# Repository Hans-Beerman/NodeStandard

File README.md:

**NodeStandard**

NodeStandard is the base for different nodes, used at the MakerSpace Leiden, to control different pieces of equipment. This repository has the following subdirs:

- **Drawings:**

- **Gerber_Files:**

This directory contains the Gerber files for production of the print. In this directory are the separate files and a *.ZIP file containing all these files. For ordering the printed circuit board, for example from JLCPCB, you only need to upload the ZIP file

Schematic of the wiring between the different modules used

- **KiCad\_files:**

The design of the PCB for the Node/Controller. De PCB in this design is not meant to be used for a real PCB. It is used as guideline for a handmade PCB

- **Photos:**

Some photos of the Node made.

- **PlatformIO\_Files:**

The source code for the Node and the display used. For the development of this software PlatformIO is used. PlatformIO is an Extension on Visual Studio Code.

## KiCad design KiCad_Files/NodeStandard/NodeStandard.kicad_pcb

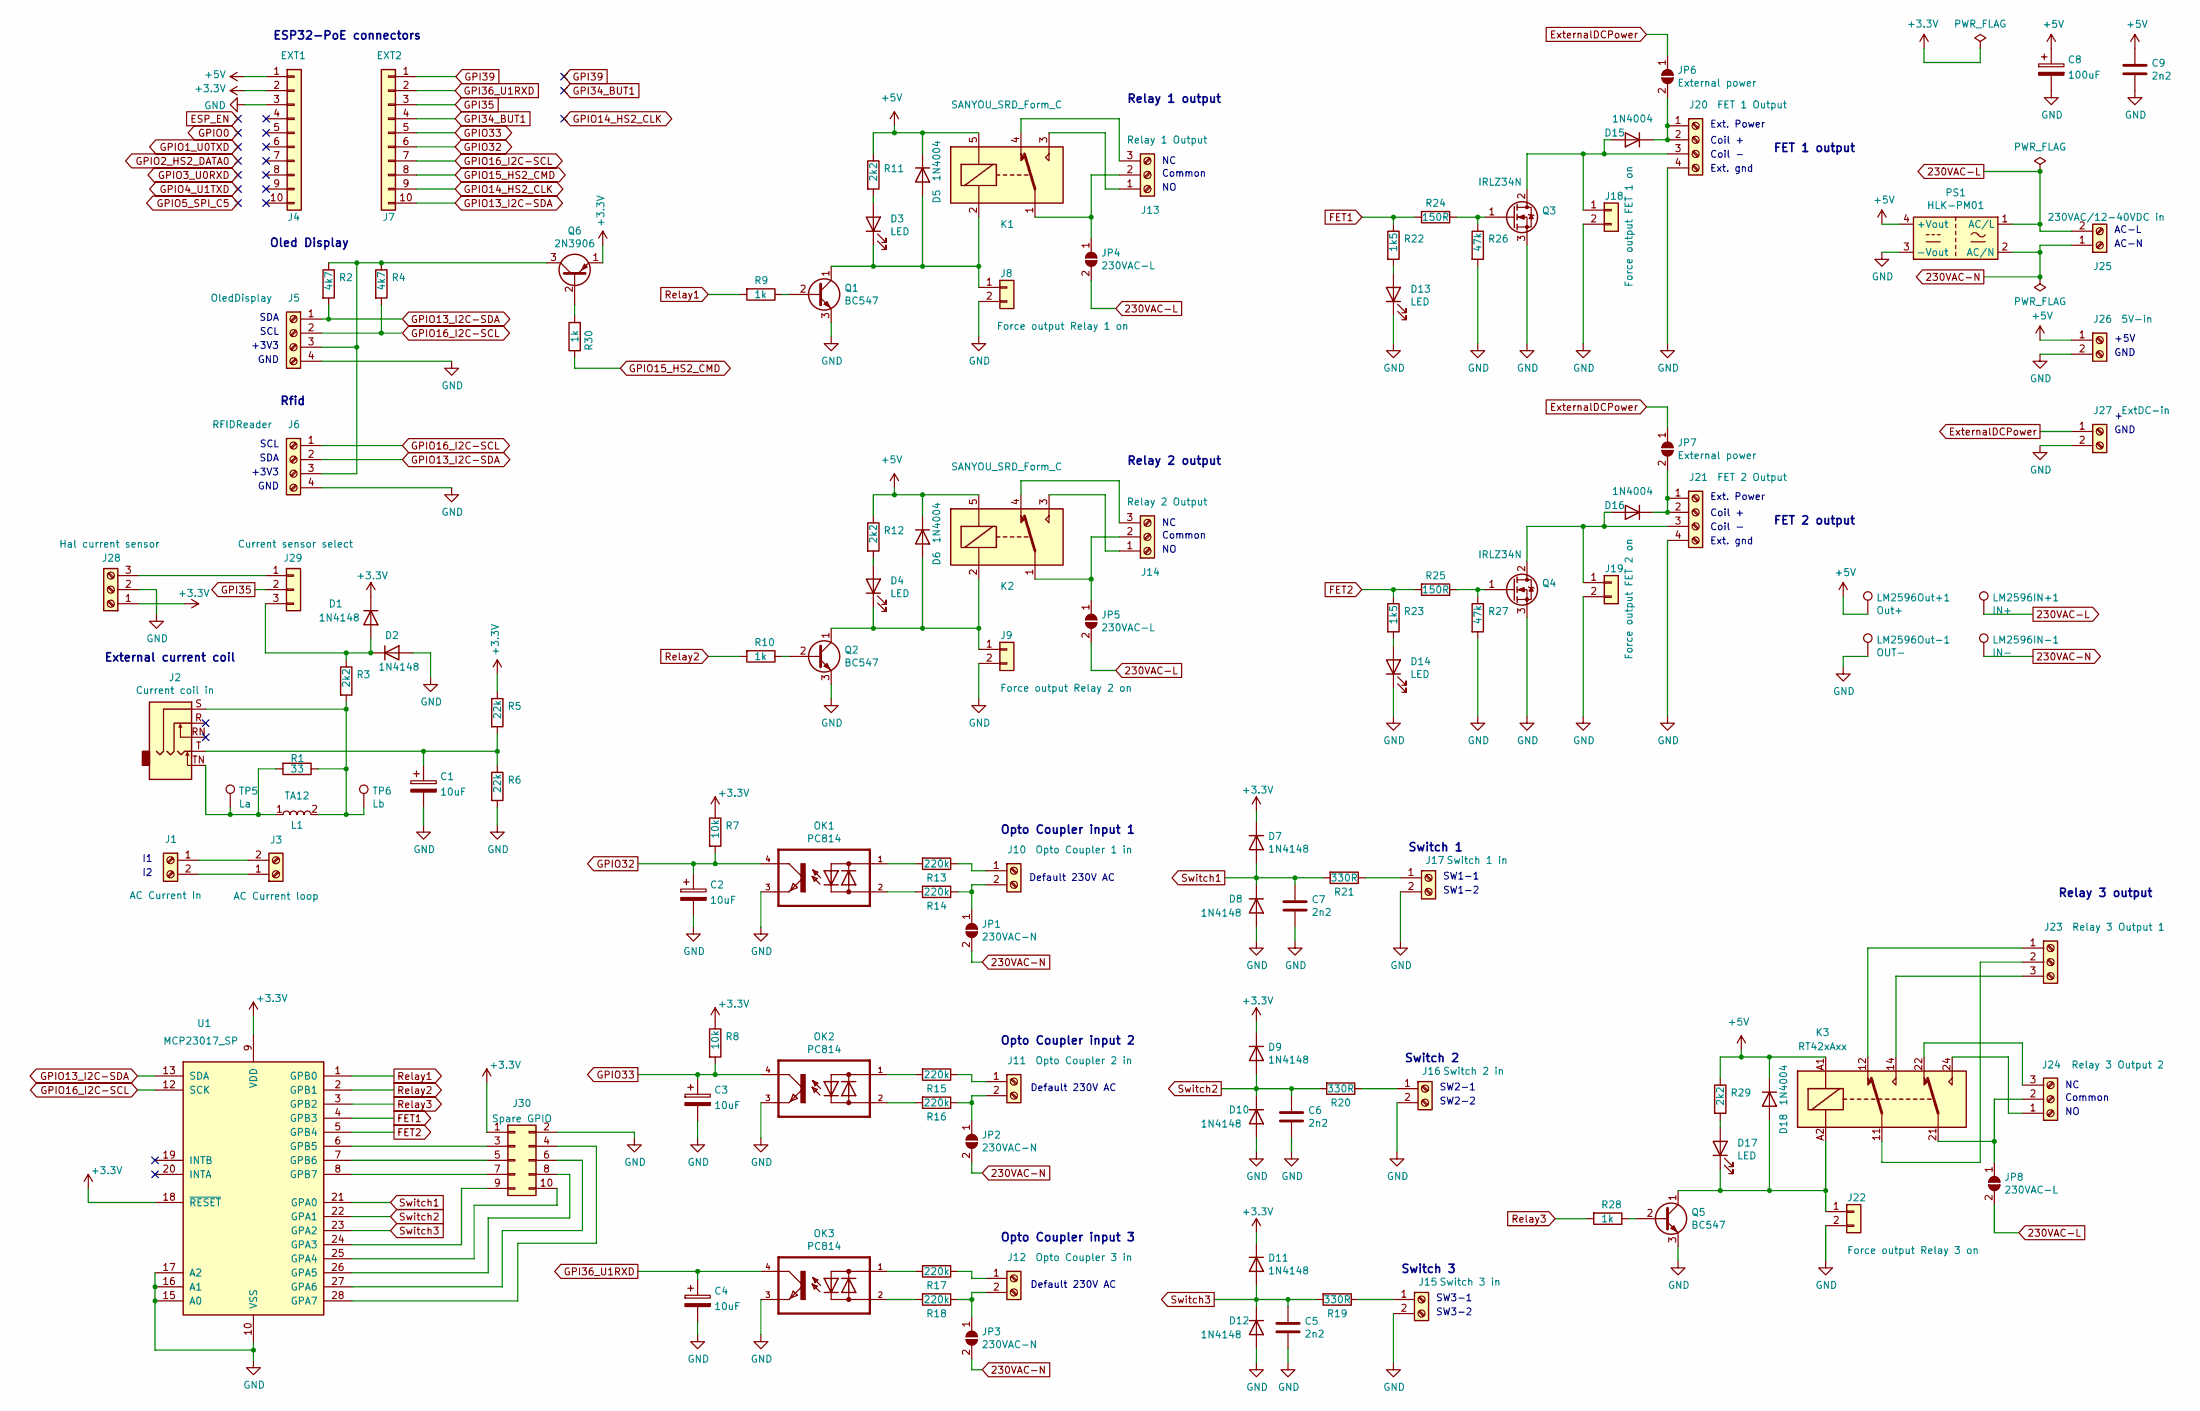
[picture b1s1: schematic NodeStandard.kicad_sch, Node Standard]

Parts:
C1, C2, C3, C4: 10uF; CP_Radial_D6.3mm_P2.50mm
C5, C6, C7, C9: 2n2; C_Disc_D5.1mm_W3.2mm_P5.00mm
C8: 100uF; CP_Radial_D6.3mm_P2.50mm
D1, D2, D7, D8, D9, D10, D11, D12: 1N4148; D_DO-35_SOD27_P7.62mm_Horizontal
D3, D4, D13, D14, D17: LED; LED_D3.0mm
D5, D6, D15, D16, D18: 1N4004; D_DO-41_SOD81_P10.16mm_Horizontal
J1: AC Current In; PhoenixContact_MSTB_2,5_2-GF-5,08_1x02_P5.08mm_Horizontal_T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
J2: Current coil in; Jack_3.5mm_CUI_FEMPM_Horizontal
J3: AC Current loop; TerminalBlock_Phoenix_MKDS-1,5-2-5.08_1x02_P5.08mm_Horizont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
J4: EXT1; PinSocket_1x10_P2.54mm_Vertical
J5: OledDisplay; TerminalBlock_Phoenix_MPT-0,5-4-2.54_1x04_P2.54mm_Horizontal
J6: RFIDReader; TerminalBlock_Phoenix_MPT-0,5-4-2.54_1x04_P2.54mm_Horizontal
J7: EXT2; PinSocket_1x10_P2.54mm_Vertical
J8: Force output Relay 1 on; PinHeader_1x02_P2.54mm_Vertical
J9: Force output Relay 2 on; PinHeader_1x02_P2.54mm_Vertical
J10: Opto Coupler 1 in; PhoenixContact_MSTB_2,5_2-GF-5,08_1x02_P5.08mm_Horizontal_T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
J11: Opto Coupler 2 in; PhoenixContact_MSTB_2,5_2-GF-5,08_1x02_P5.08mm_Horizontal_T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
J12: Opto Coupler 3 in; PhoenixContact_MSTB_2,5_2-GF-5,08_1x02_P5.08mm_Horizontal_T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
J13: Relay 1 Output; PhoenixContact_MSTB_2,5_3-GF-5,08_1x03_P5.08mm_Horizontal_T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
J14: Relay 2 Output; PhoenixContact_MSTB_2,5_3-GF-5,08_1x03_P5.08mm_Horizontal_T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
J15: Switch 3 in; TerminalBlock_Phoenix_MPT-0,5-2-2.54_1x02_P2.54mm_Horizontal
J16: Switch 2 in; TerminalBlock_Phoenix_MPT-0,5-2-2.54_1x02_P2.54mm_Horizontal
J17: Switch 1 in; TerminalBlock_Phoenix_MPT-0,5-2-2.54_1x02_P2.54mm_Horizontal
J18: Force output FET 1 on; PinHeader_1x02_P2.54mm_Vertical
J19: Force output FET 2 on; PinHeader_1x02_P2.54mm_Vertical
J20: FET 1 Output; PhoenixContact_MSTB_2,5_4-GF-5,08_1x04_P5.08mm_Horizontal_T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
J21: FET 2 Output; PhoenixContact_MSTB_2,5_4-GF-5,08_1x04_P5.08mm_Horizontal_T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
J22: Force output Relay 3 on; PinHeader_1x02_P2.54mm_Vertical
J23: Relay 3 Output 1; PhoenixContact_MSTB_2,5_3-GF-5,08_1x03_P5.08mm_Horizontal_T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
J24: Relay 3 Output 2; PhoenixContact_MSTB_2,5_3-GF-5,08_1x03_P5.08mm_Horizontal_T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
J25: 230VAC/12-40VDC in; PhoenixContact_MSTB_2,5_2-GF-5,08_1x02_P5.08mm_Horizontal_T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
J26: 5V-in; PhoenixContact_MSTB_2,5_2-GF-5,08_1x02_P5.08mm_Horizontal_T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
J27: ExtDC-in; PhoenixContact_MSTB_2,5_2-GF-5,08_1x02_P5.08mm_Horizontal_T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
J28: Hal current sensor; TerminalBlock_Phoenix_MPT-0,5-3-2.54_1x03_P2.54mm_Horizontal
J29: Current sensor select; PinHeader_1x03_P2.54mm_Vertical
J30: Spare GPIO; PinHeader_2x05_P2.54mm_Vertical
JP1, JP2, JP3: 230VAC-N; SolderJumper-2_P3mm_Open_RoundedPad
JP4, JP5, JP8: 230VAC-L; SolderJumper-2_P3mm_Open_RoundedPad
JP6, JP7: External power; SolderJumper-2_P1.3mm_Open_RoundedPad1.0x1.5mm
K1, K2: SANYOU_SRD_Form_C; Relay_SPDT_SANYOU_SRD_Series_Form_C
K3: RT42xAxx; Relay_DPDT_Schrack-RT2-FormC_RM5mm
L1: TA12; TA12-100
LM2596IN+1: IN+; TestPoint_THTPad_2.0x2.0mm_Drill1.0mm
LM2596IN-1: IN-; TestPoint_THTPad_2.0x2.0mm_Drill1.0mm
LM2596Out+1: Out+; TestPoint_THTPad_2.0x2.0mm_Drill1.0mm
LM2596Out-1: OUT-; TestPoint_THTPad_2.0x2.0mm_Drill1.0mm
OK1, OK2, OK3: PC814; DIP-4_W7.62mm
PS1: HLK-PM01; Converter_ACDC_HiLink_HLK-PMxx
Q1, Q2, Q5: BC547; TO-92_Inline
Q3, Q4: IRLZ34N; TO-220-3_Vertical
Q6: 2N3906; TO-92_Inline
R1: 33; R_Axial_DIN0207_L6.3mm_D2.5mm_P7.62mm_Horizontal
R2, R4: 4k7; R_Axial_DIN0207_L6.3mm_D2.5mm_P7.62mm_Horizontal
R3, R11, R12, R29: 2k2; R_Axial_DIN0207_L6.3mm_D2.5mm_P7.62mm_Horizontal
R5, R6: 22k; R_Axial_DIN0207_L6.3mm_D2.5mm_P7.62mm_Horizontal
R7, R8: 10k; R_Axial_DIN0207_L6.3mm_D2.5mm_P7.62mm_Horizontal
R9, R10, R28, R30: 1k; R_Axial_DIN0207_L6.3mm_D2.5mm_P7.62mm_Horizontal
R13, R14, R15, R16, R17, R18: 220k; R_Axial_DIN0516_L15.5mm_D5.0mm_P20.32mm_Horizontal
R19, R20, R21: 330R; R_Axial_DIN0207_L6.3mm_D2.5mm_P7.62mm_Horizontal
R22, R23: 1k5; R_Axial_DIN0207_L6.3mm_D2.5mm_P7.62mm_Horizontal
R24, R25: 150R; R_Axial_DIN0207_L6.3mm_D2.5mm_P7.62mm_Horizontal
R26, R27: 47k; R_Axial_DIN0207_L6.3mm_D2.5mm_P7.62mm_Horizontal
TP5: La; TestPoint_THTPad_2.5x2.5mm_Drill1.2mm
TP6: Lb; TestPoint_THTPad_2.5x2.5mm_Drill1.2mm
U1: MCP23017_SP; DIP-28_W7.62mm

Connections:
230VAC-L: J25.2, JP4.2 (B), JP5.2 (B), JP8.2 (B), LM2596IN+1.1, PS1.1 (AC/L)
230VAC-N: J25.1, JP1.2 (B), JP2.2 (B), JP3.2 (B), LM2596IN-1.1, PS1.2 (AC/N)
+3V3: D1.1 (K), D7.1 (K), D9.1 (K), D11.1 (K), J4.2, J28.1, J30.1, Q6.1 (E), R5.1, R7.1, R8.1, U1.9 (VDD), U1.18 (~RESET)
+5V: C8.1, C9.1, D5.1 (K), D6.1 (K), D18.1 (K), J4.1, J26.1, K1.5, K2.5, K3.A1, LM2596Out+1.1, PS1.4 (+Vout), R11.1, R12.1, R29.1
ExternalDCPower: J27.1, JP6.1 (A), JP7.1 (A)
FET1: R22.1, R24.2, U1.4 (GPB3)
FET2: R23.1, R25.2, U1.5 (GPB4)
GND: C1.2, C2.2, C3.2, C4.2, C5.2, C6.2, C7.2, C8.2, C9.2, D2.2 (A), D8.2 (A), D10.2 (A), D12.2 (A), D13.1 (K), D14.1 (K), J4.3, J5.4, J6.4, J8.2, J9.2, J15.2, J16.2, J17.2, J18.2, J19.2, J20.4, J21.4, J22.2, J26.2, J27.2, J28.2, J30.2, LM2596Out-1.1, OK1.3 (E), OK2.3 (E), OK3.3 (E), PS1.3 (-Vout), Q1.3 (E), Q2.3 (E), Q3.3 (S), Q4.3 (S), Q5.3 (E), R6.2, R26.2, R27.2, U1.10 (VSS), U1.15 (A0), U1.16 (A1), U1.17 (A2)
GPI34_BUT1: J7.4
GPI35: J7.3, J29.2
GPI36_U1RXD: C4.1, J7.2, OK3.4 (C)
GPI39: J7.1
GPIO13_I2C-SDA: J5.1, J6.2, J7.10, R2.2, U1.13 (SDA)
GPIO14_HS2_CLK: J7.9
GPIO15_HS2_CMD: J7.8, R30.1
GPIO16_I2C-SCL: J5.2, J6.1, J7.7, R4.2, U1.12 (SCK)
GPIO32: C2.1, J7.6, OK1.4 (C), R7.2
GPIO33: C3.1, J7.5, OK2.4 (C), R8.2
unnamed: C1.1, J2.T, R5.2, R6.1
unnamed: D1.2 (A), D2.1 (K), J29.3, R3.1
unnamed: D3.1 (K), D5.2 (A), J8.1, K1.2, Q1.1 (C)
unnamed: D3.2 (A), R11.2
unnamed: D4.1 (K), D6.2 (A), J9.1, K2.2, Q2.1 (C)
unnamed: D4.2 (A), R12.2
unnamed: D13.2 (A), R22.2
unnamed: D14.2 (A), R23.2
unnamed: D15.1 (K), J20.1, J20.2, JP6.2 (B)
unnamed: D15.2 (A), J18.1, J20.3, Q3.2 (D)
unnamed: D16.1 (K), J21.1, J21.2, JP7.2 (B)
unnamed: D16.2 (A), J19.1, J21.3, Q4.2 (D)
unnamed: D17.1 (K), D18.2 (A), J22.1, K3.A2, Q5.1 (C)
unnamed: D17.2 (A), R29.2
unnamed: J1.1, J3.2
unnamed: J1.2, J3.1
unnamed: J2.S, L1.2, R1.1, R3.2, TP6.1
unnamed: J2.TN, L1.1, R1.2, TP5.1
unnamed: J5.3, J6.3, Q6.3 (C), R2.1, R4.1
unnamed: J10.1, R13.1
unnamed: J10.2, JP1.1 (A), R14.1
unnamed: J11.1, R15.1
unnamed: J11.2, JP2.1 (A), R16.1
unnamed: J12.1, R17.1
unnamed: J12.2, JP3.1 (A), R18.1
unnamed: J13.1, K1.3
unnamed: J13.2, JP4.1 (A), K1.1
unnamed: J13.3, K1.4
unnamed: J14.1, K2.3
unnamed: J14.2, JP5.1 (A), K2.1
unnamed: J14.3, K2.4
unnamed: J15.1, R19.1
unnamed: J16.1, R20.1
unnamed: J17.1, R21.1
unnamed: J23.1, K3.12
unnamed: J23.2, K3.11
unnamed: J23.3, K3.14
unnamed: J24.1, K3.24
unnamed: J24.2, JP8.1 (A), K3.21
unnamed: J24.3, K3.22
unnamed: J28.3, J29.1
unnamed: J30.3, U1.6 (GPB5)
unnamed: J30.4, U1.28 (GPA7)
unnamed: J30.5, U1.7 (GPB6)
unnamed: J30.6, U1.27 (GPA6)
unnamed: J30.7, U1.8 (GPB7)
unnamed: J30.8, U1.26 (GPA5)
unnamed: J30.9, U1.24 (GPA3)
unnamed: J30.10, U1.25 (GPA4)
unnamed: OK1.1 (AC1), R13.2
unnamed: OK1.2 (AC2), R14.2
unnamed: OK2.1 (AC1), R15.2
unnamed: OK2.2 (AC2), R16.2
unnamed: OK3.1 (AC1), R17.2
unnamed: OK3.2 (AC2), R18.2
unnamed: Q1.2 (B), R9.1
unnamed: Q2.2 (B), R10.1
unnamed: Q3.1 (G), R24.1, R26.1
unnamed: Q4.1 (G), R25.1, R27.1
unnamed: Q5.2 (B), R28.1
unnamed: Q6.2 (B), R30.2
Relay1: R9.2, U1.1 (GPB0)
Relay2: R10.2, U1.2 (GPB1)
Relay3: R28.2, U1.3 (GPB2)
Switch1: C7.1, D7.2 (A), D8.1 (K), R21.2, U1.21 (GPA0)
Switch2: C6.1, D9.2 (A), D10.1 (K), R20.2, U1.22 (GPA1)
Switch3: C5.1, D11.2 (A), D12.1 (K), R19.2, U1.23 (GPA2)

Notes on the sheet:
SDA
GND
+3V3
Ext. gnd
SW3-2
Switch 3
+5V
Rfid
SCL
SW2-1
ESP32-PoE connectors
Common
AC-L
Default 230V AC
Ext. Power
Coil +
Switch 2
Relay 2 output
SW2-2
External current coil
SW1-1
Coil -
Switch 1
SW1-2
Relay 3 output
FET 1 output
Oled Display
Opto Coupler input 2
Opto Coupler input 1
AC-N
Relay 1 output
Opto Coupler input 3
FET 2 output
SW3-1

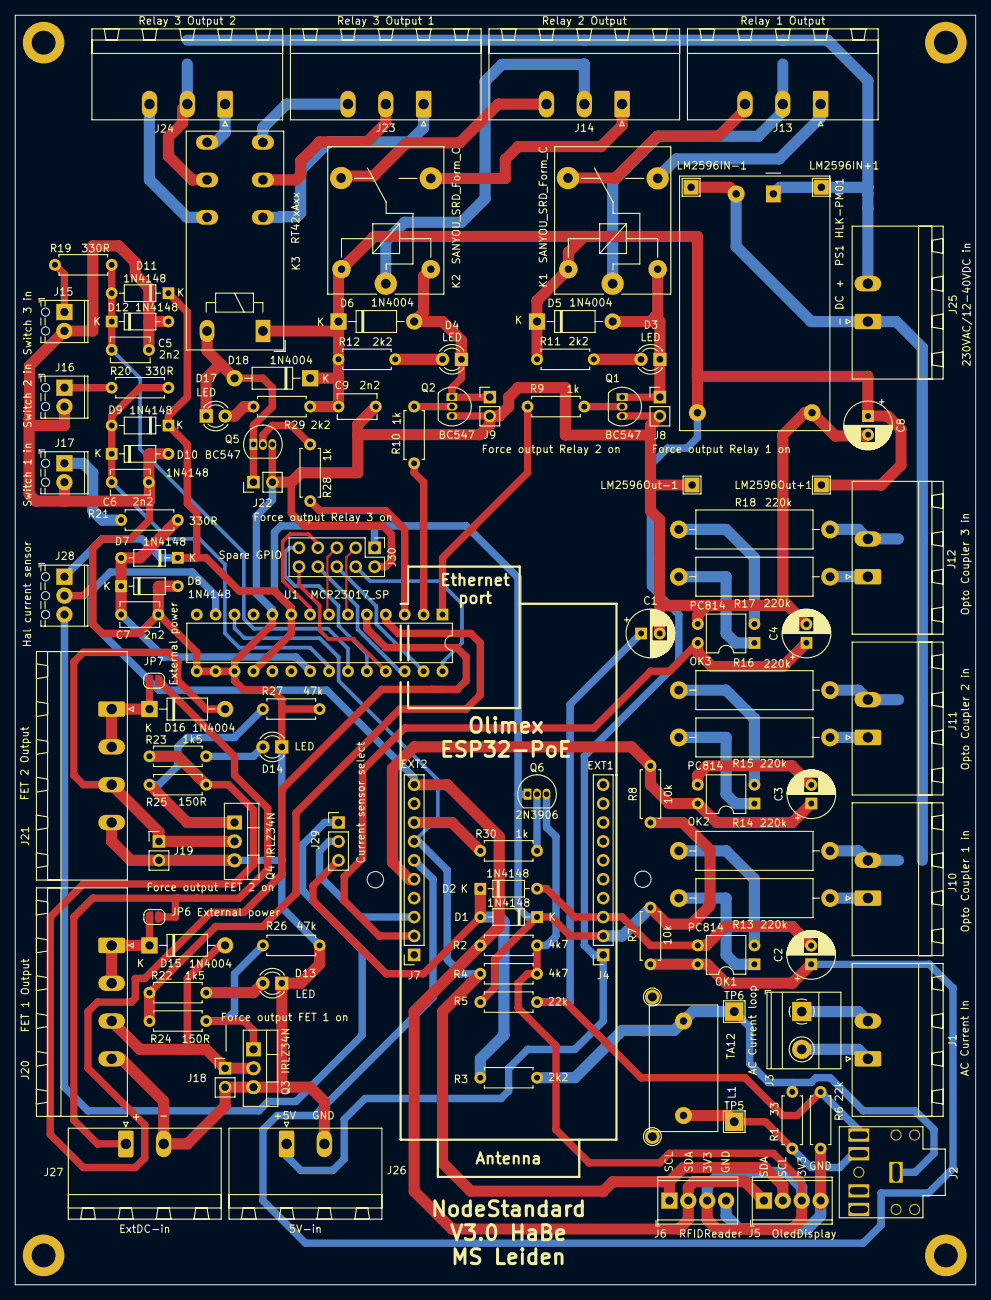
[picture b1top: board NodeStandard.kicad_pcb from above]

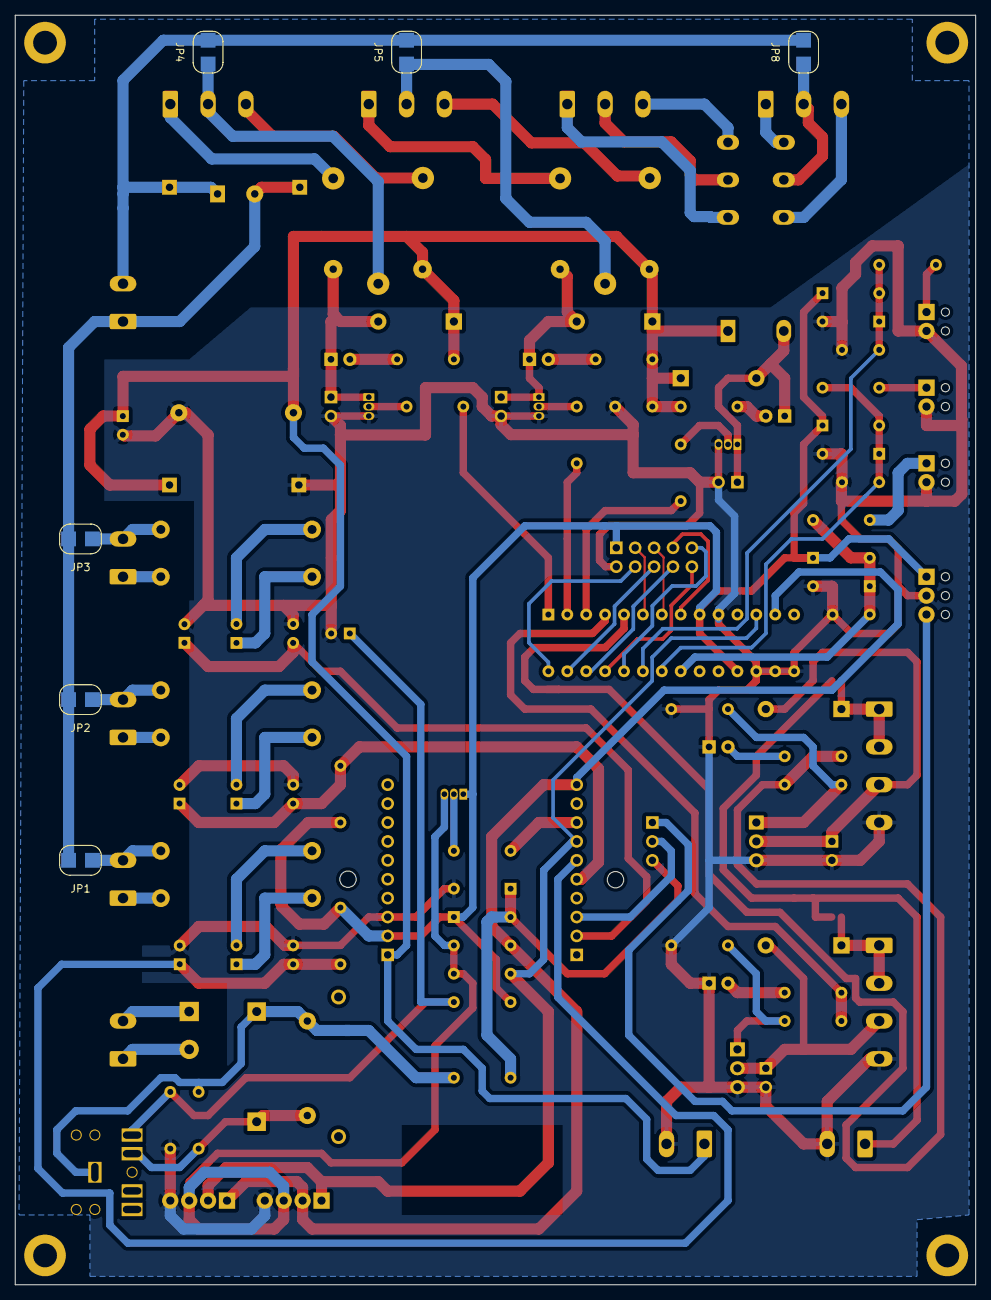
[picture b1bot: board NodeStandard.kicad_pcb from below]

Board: 2 copper layers, 129.0 x 170.6 mm, 116 parts (6 on the bottom side), 82 nets.

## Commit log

2020-11-12 First design
2020-11-12 Added .gitignore
2020-11-12 updated README.nd
2020-11-24 V0.3.0.0 Work in progress, layout of components on PCB added
2020-11-24 V0.4 Work in progress, added some footprints with 3D models
2020-12-04 V0.5 Work in progress, first version PCB design, no silk screen yet
2020-12-13 V0.6 Silk screen added, ready for first trial with real print
2021-01-05 V0.7 a few changes needed for the production of the PCB
2021-01-06 V0.8 moved a mounting hole and generated Gerber files
2021-02-18 Version 0.9: 2 typo's in silkscreen labels corrected
2021-02-20 Version 0.9 corrected typo's on silk screen added ESP32 model on silk screen + added 2 holes to fixate ESP32 with tie wrap or so
2021-04-23 V0.0.9.0 added a number of improvements
2022-01-16 Third (fysical) version of the PCB for this node. Added a header to provide access to some free (currently not used GPIO ports), also made the holes for the coil a little bit wider
